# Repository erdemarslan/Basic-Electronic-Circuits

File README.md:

# Basic-Electronic-Circuits
Basic electronic circuits for students and who learning electronics.

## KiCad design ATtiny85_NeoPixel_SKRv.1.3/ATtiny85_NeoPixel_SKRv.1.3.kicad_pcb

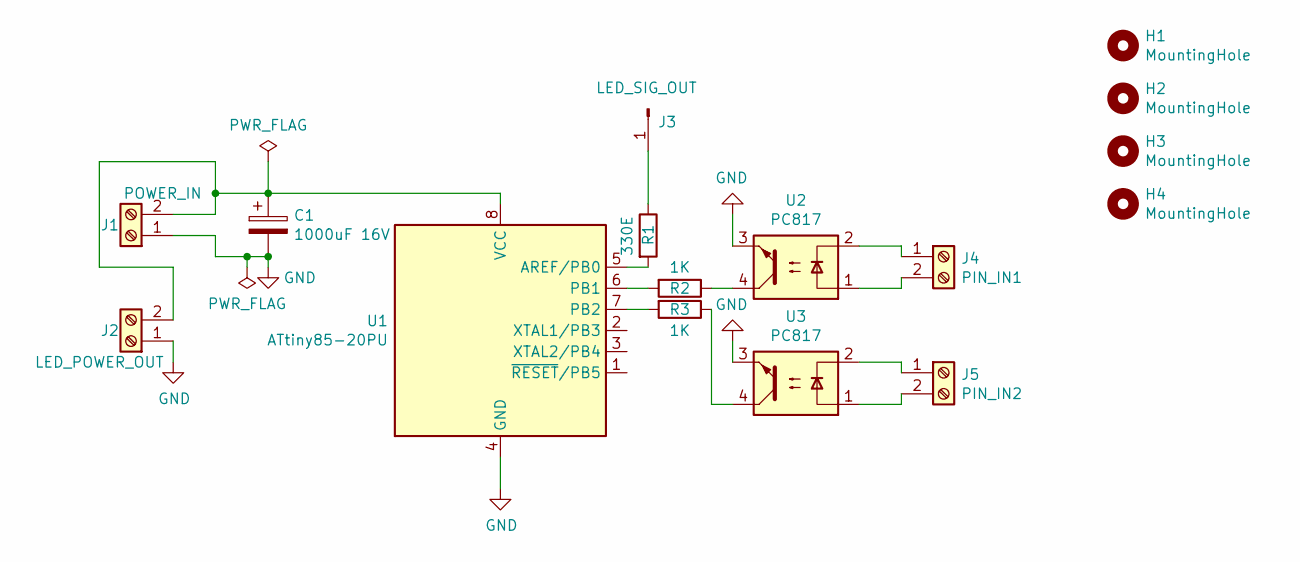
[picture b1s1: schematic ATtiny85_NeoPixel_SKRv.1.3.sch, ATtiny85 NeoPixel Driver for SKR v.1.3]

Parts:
C1: 1000uF 16V; CP_Radial_D8.0mm_P3.80mm
H1, H2, H3, H4: MountingHole; MountingHole_3.2mm_M3
J1: POWER_IN; TerminalBlock_Altech_AK300-2_P5.00mm
J2: LED_POWER_OUT; TerminalBlock_Altech_AK300-2_P5.00mm
J3: LED_SIG_OUT; PinHeader_1x01_P2.54mm_Vertical
J4: PIN_IN1; TerminalBlock_Altech_AK300-2_P5.00mm
J5: PIN_IN2; TerminalBlock_Altech_AK300-2_P5.00mm
R1: 330E; R_Axial_DIN0207_L6.3mm_D2.5mm_P2.54mm_Vertical
R2, R3: 1K; R_Axial_DIN0207_L6.3mm_D2.5mm_P2.54mm_Vertical
U1: ATtiny85-20PU; DIP-8_W7.62mm
U2, U3: PC817; DIP-4_W7.62mm

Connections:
GND: C1.2, J1.1, J2.1, U1.4 (GND), U2.3, U3.3
unnamed: C1.1, J1.2, J2.2, U1.8 (VCC)
unnamed: J3.1, R1.1
unnamed: J4.1, U2.2
unnamed: J4.2, U2.1
unnamed: J5.1, U3.2
unnamed: J5.2, U3.1
unnamed: R1.2, U1.5 (AREF/PB0)
unnamed: R2.1, U2.4
unnamed: R2.2, U1.6 (PB1)
unnamed: R3.1, U3.4
unnamed: R3.2, U1.7 (PB2)

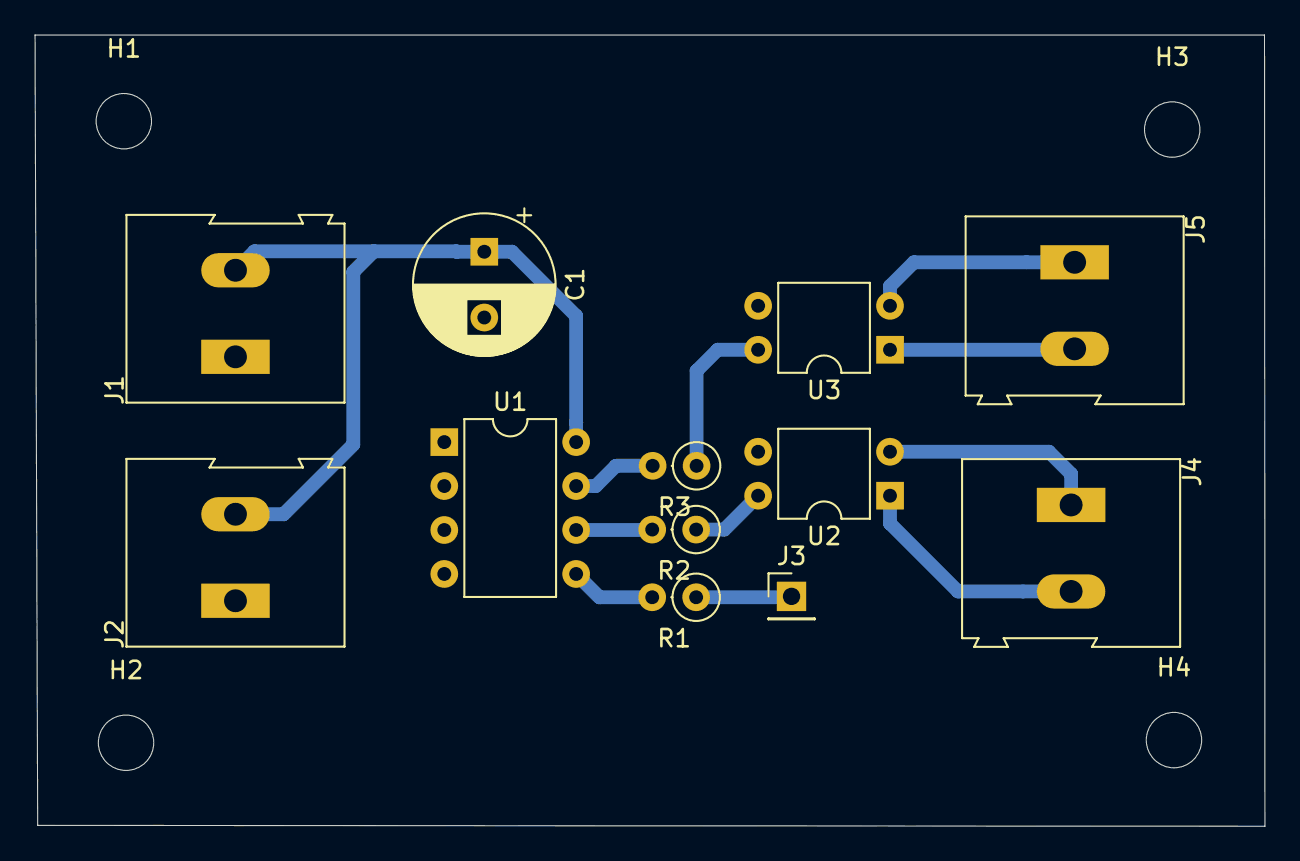
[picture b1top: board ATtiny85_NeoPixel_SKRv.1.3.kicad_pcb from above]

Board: 2 copper layers, 71.1 x 45.7 mm, 16 parts (0 on the bottom side), 12 nets.

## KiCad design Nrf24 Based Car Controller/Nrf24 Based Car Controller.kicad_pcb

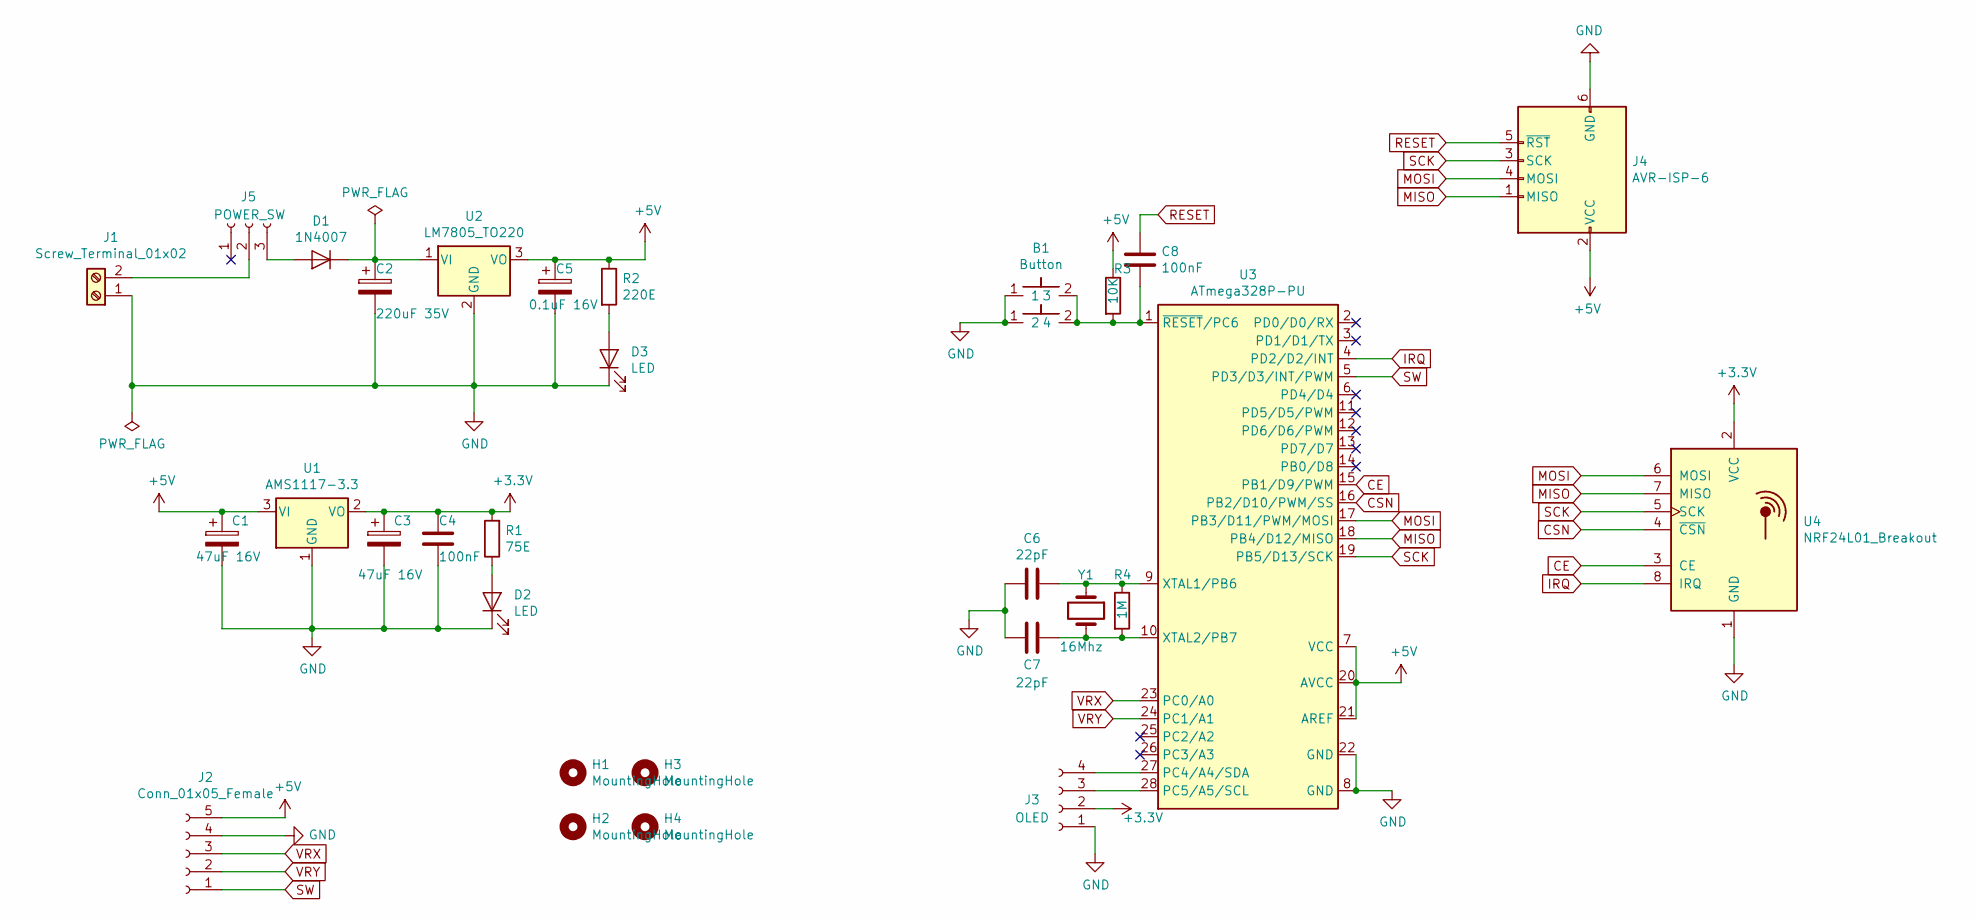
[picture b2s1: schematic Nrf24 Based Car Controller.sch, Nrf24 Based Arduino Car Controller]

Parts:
B1: Button; SW_PUSH_6mm
C1, C3: 47uF 16V; CP_Radial_D6.3mm_P2.50mm
C2: 220uF 35V; CP_Radial_D6.3mm_P2.50mm
C4, C8: 100nF; C_Disc_D6.0mm_W2.5mm_P5.00mm
C5: 0.1uF 16V; CP_Radial_D6.3mm_P2.50mm
C6, C7: 22pF; C_Disc_D3.0mm_W1.6mm_P2.50mm
D1: 1N4007; D_DO-41_SOD81_P10.16mm_Horizontal
D2, D3: LED; LED_D5.0mm
H1, H2, H3, H4: MountingHole; MountingHole_3.2mm_M3
J1: Screw_Terminal_01x02; TerminalBlock_bornier-2_P5.08mm
J2: Conn_01x05_Female; PinHeader_1x05_P2.54mm_Vertical
J3: OLED; PinHeader_1x04_P2.54mm_Vertical
J4: AVR-ISP-6; IDC-Header_2x03_P2.54mm_Vertical
J5: POWER_SW; PinHeader_1x03_P2.00mm_Vertical
R1: 75E; R_Axial_DIN0207_L6.3mm_D2.5mm_P7.62mm_Horizontal
R2: 220E; R_Axial_DIN0207_L6.3mm_D2.5mm_P7.62mm_Horizontal
R3: 10K; R_Axial_DIN0207_L6.3mm_D2.5mm_P7.62mm_Horizontal
R4: 1M; R_Axial_DIN0207_L6.3mm_D2.5mm_P7.62mm_Horizontal
U1: AMS1117-3.3; SOT-223-3_TabPin2
U2: LM7805_TO220; TO-220-3_Vertical
U3: ATmega328P-PU; DIP-28_W7.62mm
U4: NRF24L01_Breakout; nRF24L01_Breakout
Y1: 16Mhz; Crystal_HC49-4H_Vertical

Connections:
+3V3: C3.1, C4.2, J3.2, R1.2, U1.2 (VO), U4.2 (VCC)
+5V: C1.1, C5.1, J2.5, J4.2 (VCC), R2.1, R3.1, U1.3 (VI), U2.3 (VO), U3.7 (VCC), U3.20 (AVCC), U3.21 (AREF)
CE: U3.15 (PB1/D9/PWM), U4.3 (CE)
CSN: U3.16 (PB2/D10/PWM/SS), U4.4 (~CSN)
GND: B1.1, C1.2, C2.2, C3.2, C4.1, C5.2, C6.2, C7.2, D2.1 (K), D3.1 (K), J1.1, J2.4, J3.1, J4.6 (GND), U1.1 (GND), U2.2 (GND), U3.8 (GND), U3.22 (GND), U4.1 (GND)
IRQ: U3.4 (PD2/D2/INT), U4.8 (IRQ)
MISO: J4.1 (MISO), U3.18 (PB4/D12/MISO), U4.7 (MISO)
MOSI: J4.4 (MOSI), U3.17 (PB3/D11/PWM/MOSI), U4.6 (MOSI)
unnamed: B1.2 (3), C8.1, R3.2, U3.1 (~RESET~/PC6)
unnamed: C2.1, D1.1 (K), U2.1 (VI)
unnamed: C6.1, R4.1, U3.9 (XTAL1/PB6), Y1.1
unnamed: C7.1, R4.2, U3.10 (XTAL2/PB7), Y1.2
unnamed: D1.2 (A), J5.3
unnamed: D2.2 (A), R1.1
unnamed: D3.2 (A), R2.2
unnamed: J1.2, J5.2
unnamed: J3.3, U3.28 (PC5/A5/SCL)
unnamed: J3.4, U3.27 (PC4/A4/SDA)
RESET: C8.2, J4.5 (~RST)
SCK: J4.3 (SCK), U3.19 (PB5/D13/SCK), U4.5 (SCK)
SW: J2.1, U3.5 (PD3/D3/INT/PWM)
VRX: J2.3, U3.23 (PC0/A0)
VRY: J2.2, U3.24 (PC1/A1)

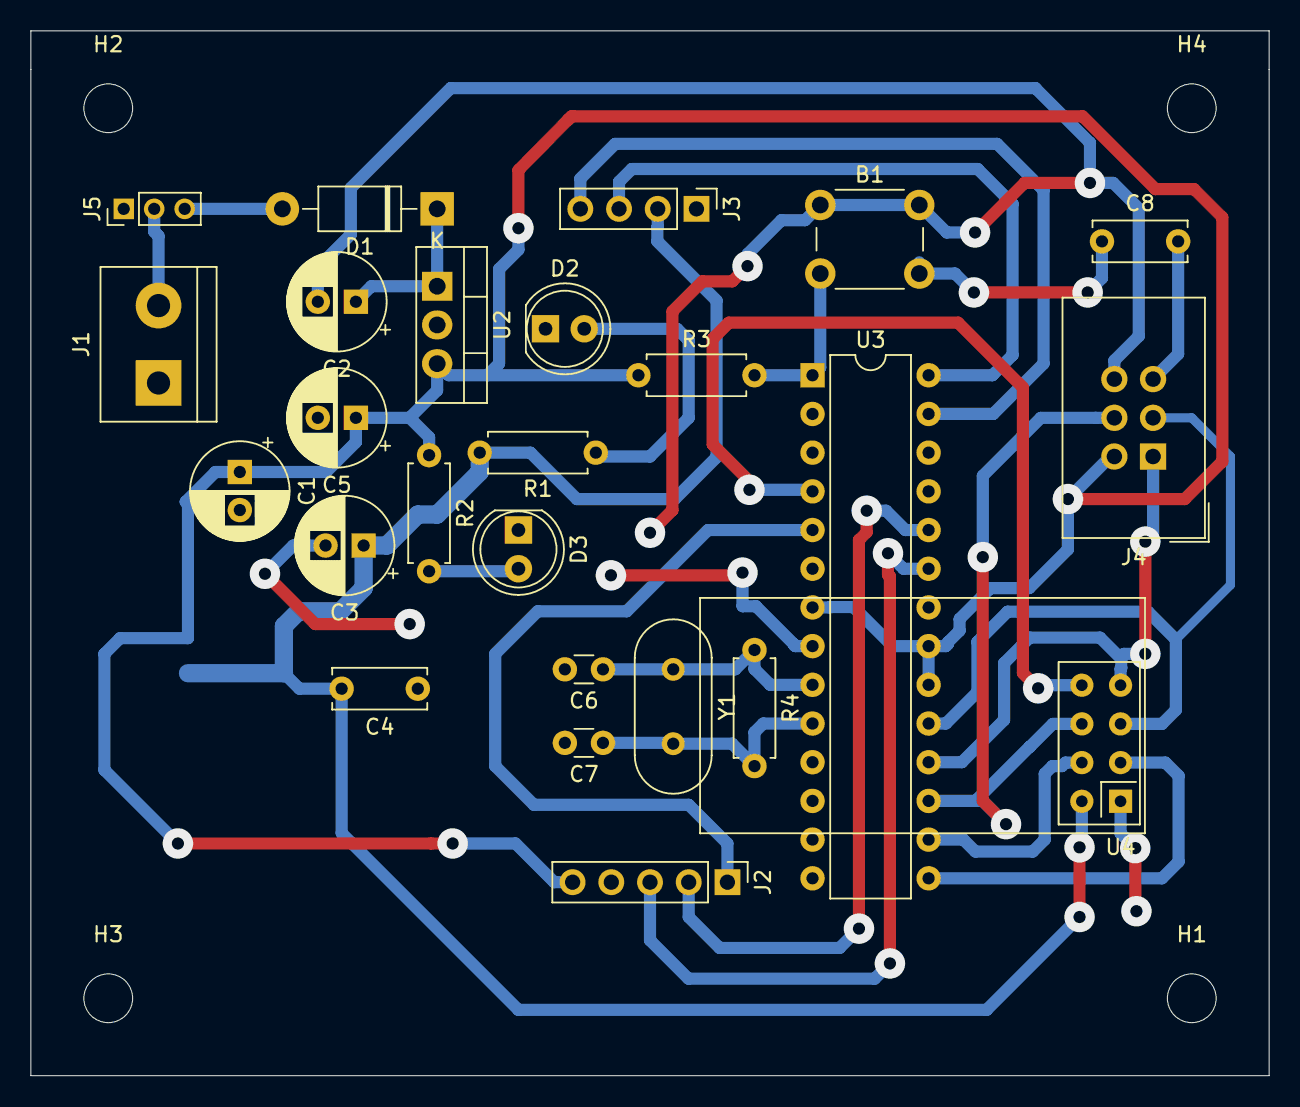
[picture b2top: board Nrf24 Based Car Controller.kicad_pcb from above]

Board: 2 copper layers, 81.3 x 68.6 mm, 30 parts (1 on the bottom side), 23 nets.

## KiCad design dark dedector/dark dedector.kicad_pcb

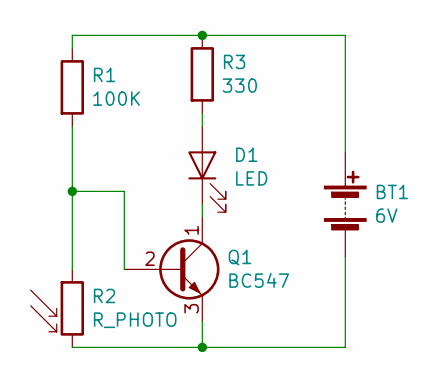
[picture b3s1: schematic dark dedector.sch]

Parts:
BT1: 6V; TerminalBlock_bornier-2_P5.08mm
D1: LED; LED_D5.0mm_Clear
Q1: BC547; TO-92_Inline
R1: 100K; R_Axial_DIN0414_L11.9mm_D4.5mm_P20.32mm_Horizontal
R2: R_PHOTO; R_LDR_4.9x4.2mm_P2.54mm_Vertical
R3: 330; R_Axial_DIN0414_L11.9mm_D4.5mm_P20.32mm_Horizontal

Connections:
unnamed: BT1.1 (+), R1.1, R3.1
unnamed: BT1.2 (-), Q1.3 (E), R2.2
unnamed: D1.1 (K), Q1.1 (C)
unnamed: D1.2 (A), R3.2
unnamed: Q1.2 (B), R1.2, R2.1

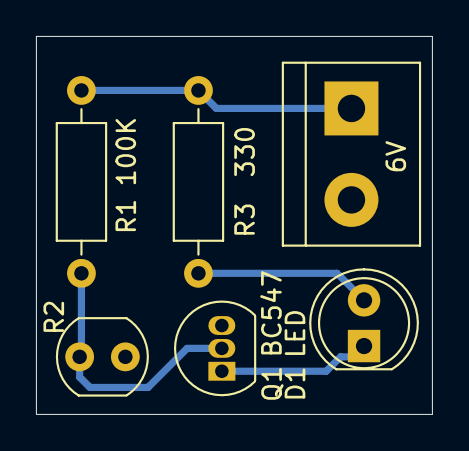
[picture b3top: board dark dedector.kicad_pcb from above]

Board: 2 copper layers, 22.0 x 21.0 mm, 6 parts (0 on the bottom side), 5 nets.

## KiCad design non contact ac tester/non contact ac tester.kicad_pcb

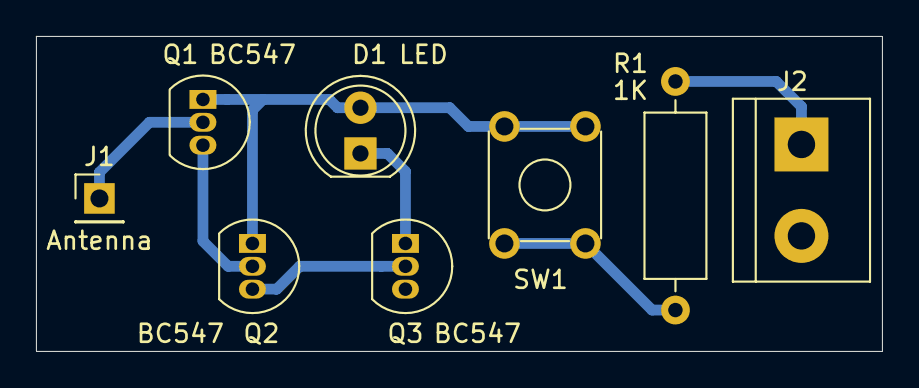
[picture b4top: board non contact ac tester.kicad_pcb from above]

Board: 2 copper layers, 47.0 x 17.5 mm, 8 parts (0 on the bottom side), 8 nets.

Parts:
D1: LED; LED_D5.0mm_FlatTop
J1: Antenna; PinHeader_1x01_P2.54mm_Vertical
J2: Screw_Terminal_01x02; TerminalBlock_bornier-2_P5.08mm
Q1, Q2, Q3: BC547; TO-92_Inline
R1: 1K; R_Axial_DIN0309_L9.0mm_D3.2mm_P12.70mm_Horizontal
SW1: SW_Push_Dual; SW_TH_Tactile_Omron_B3F-10xx

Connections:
+9V: J2.1, R1.1
GND: J2.2, Q3.3
unnamed: D1.1, Q3.1
unnamed: D1.2, Q1.1, Q2.1, SW1.1, SW1.3
unnamed: J1.1, Q1.2
unnamed: Q1.3, Q2.2
unnamed: Q2.3, Q3.2
unnamed: R1.2, SW1.2, SW1.4

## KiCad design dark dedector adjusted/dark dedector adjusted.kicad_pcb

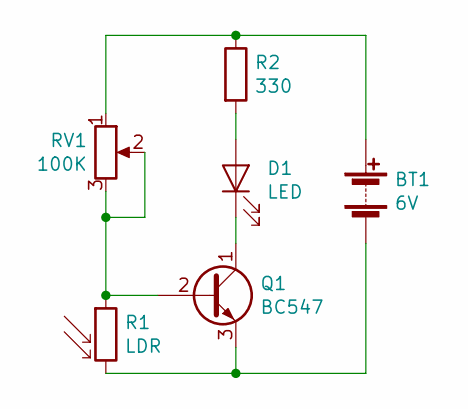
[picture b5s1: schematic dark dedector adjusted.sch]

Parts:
BT1: 6V; TerminalBlock_bornier-2_P5.08mm
D1: LED; LED_D5.0mm
Q1: BC547; TO-92_Inline
R1: LDR; R_LDR_5.0x4.1mm_P3mm_Vertical
R2: 330; R_Axial_DIN0204_L3.6mm_D1.6mm_P7.62mm_Horizontal
RV1: 100K; Potentiometer_ACP_CA9-H5_Horizontal

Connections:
unnamed: BT1.1 (+), R2.1, RV1.1
unnamed: BT1.2 (-), Q1.3 (E), R1.2
unnamed: D1.1 (K), Q1.1 (C)
unnamed: D1.2 (A), R2.2
unnamed: Q1.2 (B), R1.1, RV1.2, RV1.3

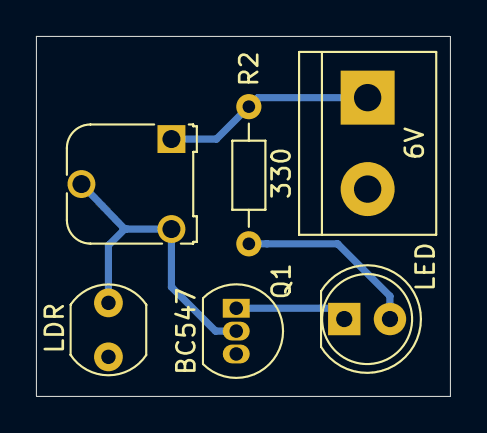
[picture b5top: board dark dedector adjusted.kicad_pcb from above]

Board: 2 copper layers, 23.0 x 20.0 mm, 6 parts (0 on the bottom side), 5 nets.

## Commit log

2020-11-04 first initalize
2020-11-04 new projects
